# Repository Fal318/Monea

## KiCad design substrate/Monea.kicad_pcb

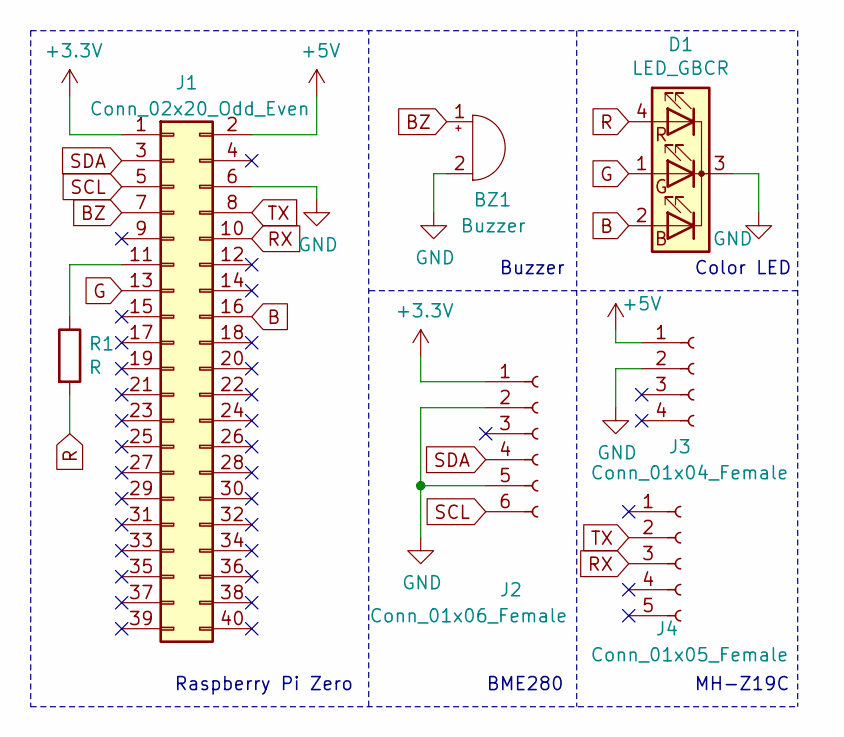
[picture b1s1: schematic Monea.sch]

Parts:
BZ1: Buzzer; Buzzer_12x9.5RM7.6
D1: LED_GBCR; LED_D5.0mm-4_RGB
J1: Conn_02x20_Odd_Even; PinSocket_2x40_P2.54mm_Vertical
J2: Conn_01x06_Female; PinSocket_1x06_P2.54mm_Vertical
J3: Conn_01x04_Female; PinSocket_1x04_P2.54mm_Vertical
J4: Conn_01x05_Female; PinSocket_1x05_P2.54mm_Vertical
R1: R; R_Axial_DIN0204_L3.6mm_D1.6mm_P5.08mm_Horizontal

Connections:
+3V3: J1.1, J2.1
+5V: J1.2, J3.1
B: D1.2 (BA), J1.16
BZ: BZ1.1 (-), J1.7
G: D1.1 (GA), J1.13
GND: BZ1.2 (+), D1.3 (K), J1.6, J2.2, J2.5, J3.2
unnamed: J1.11, R1.1
R: D1.4 (RA), R1.2
RX: J1.10, J4.3
SCL: J1.5, J2.6
SDA: J1.3, J2.4
TX: J1.8, J4.2

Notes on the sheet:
BME280
MH-Z19C
Raspberry Pi Zero
Buzzer
Color LED

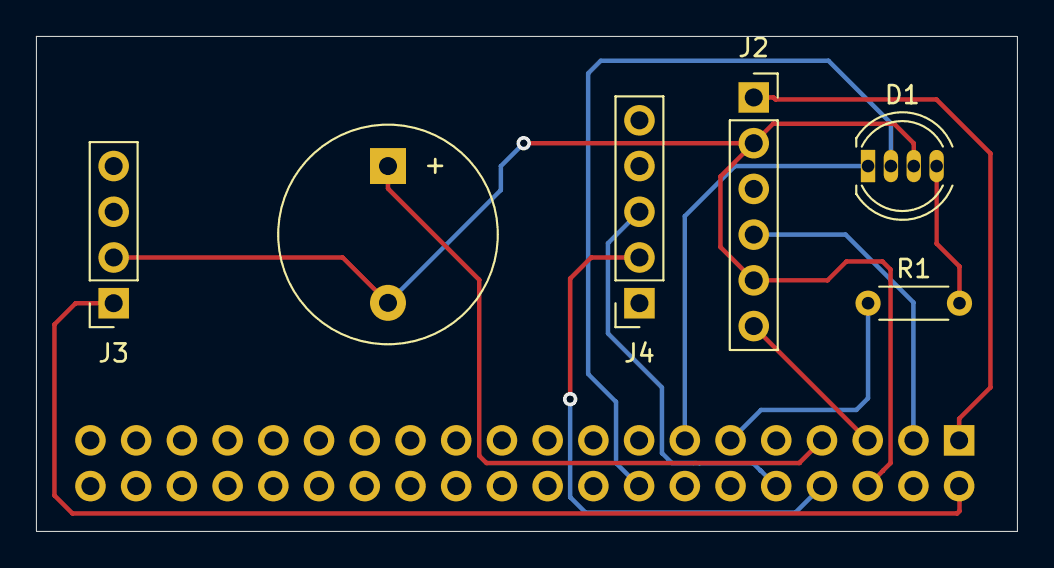
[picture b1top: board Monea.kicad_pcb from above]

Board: 2 copper layers, 54.5 x 27.5 mm, 7 parts (1 on the bottom side), 12 nets.

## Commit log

2021-09-28 :tada:回路図の作成
2021-10-26 :construction: WIP
2022-01-18 :bookmark:v1
2022-01-18 :horse:ブザーの間隔の修正
2022-01-18 :bug:欠損値処理の追加
